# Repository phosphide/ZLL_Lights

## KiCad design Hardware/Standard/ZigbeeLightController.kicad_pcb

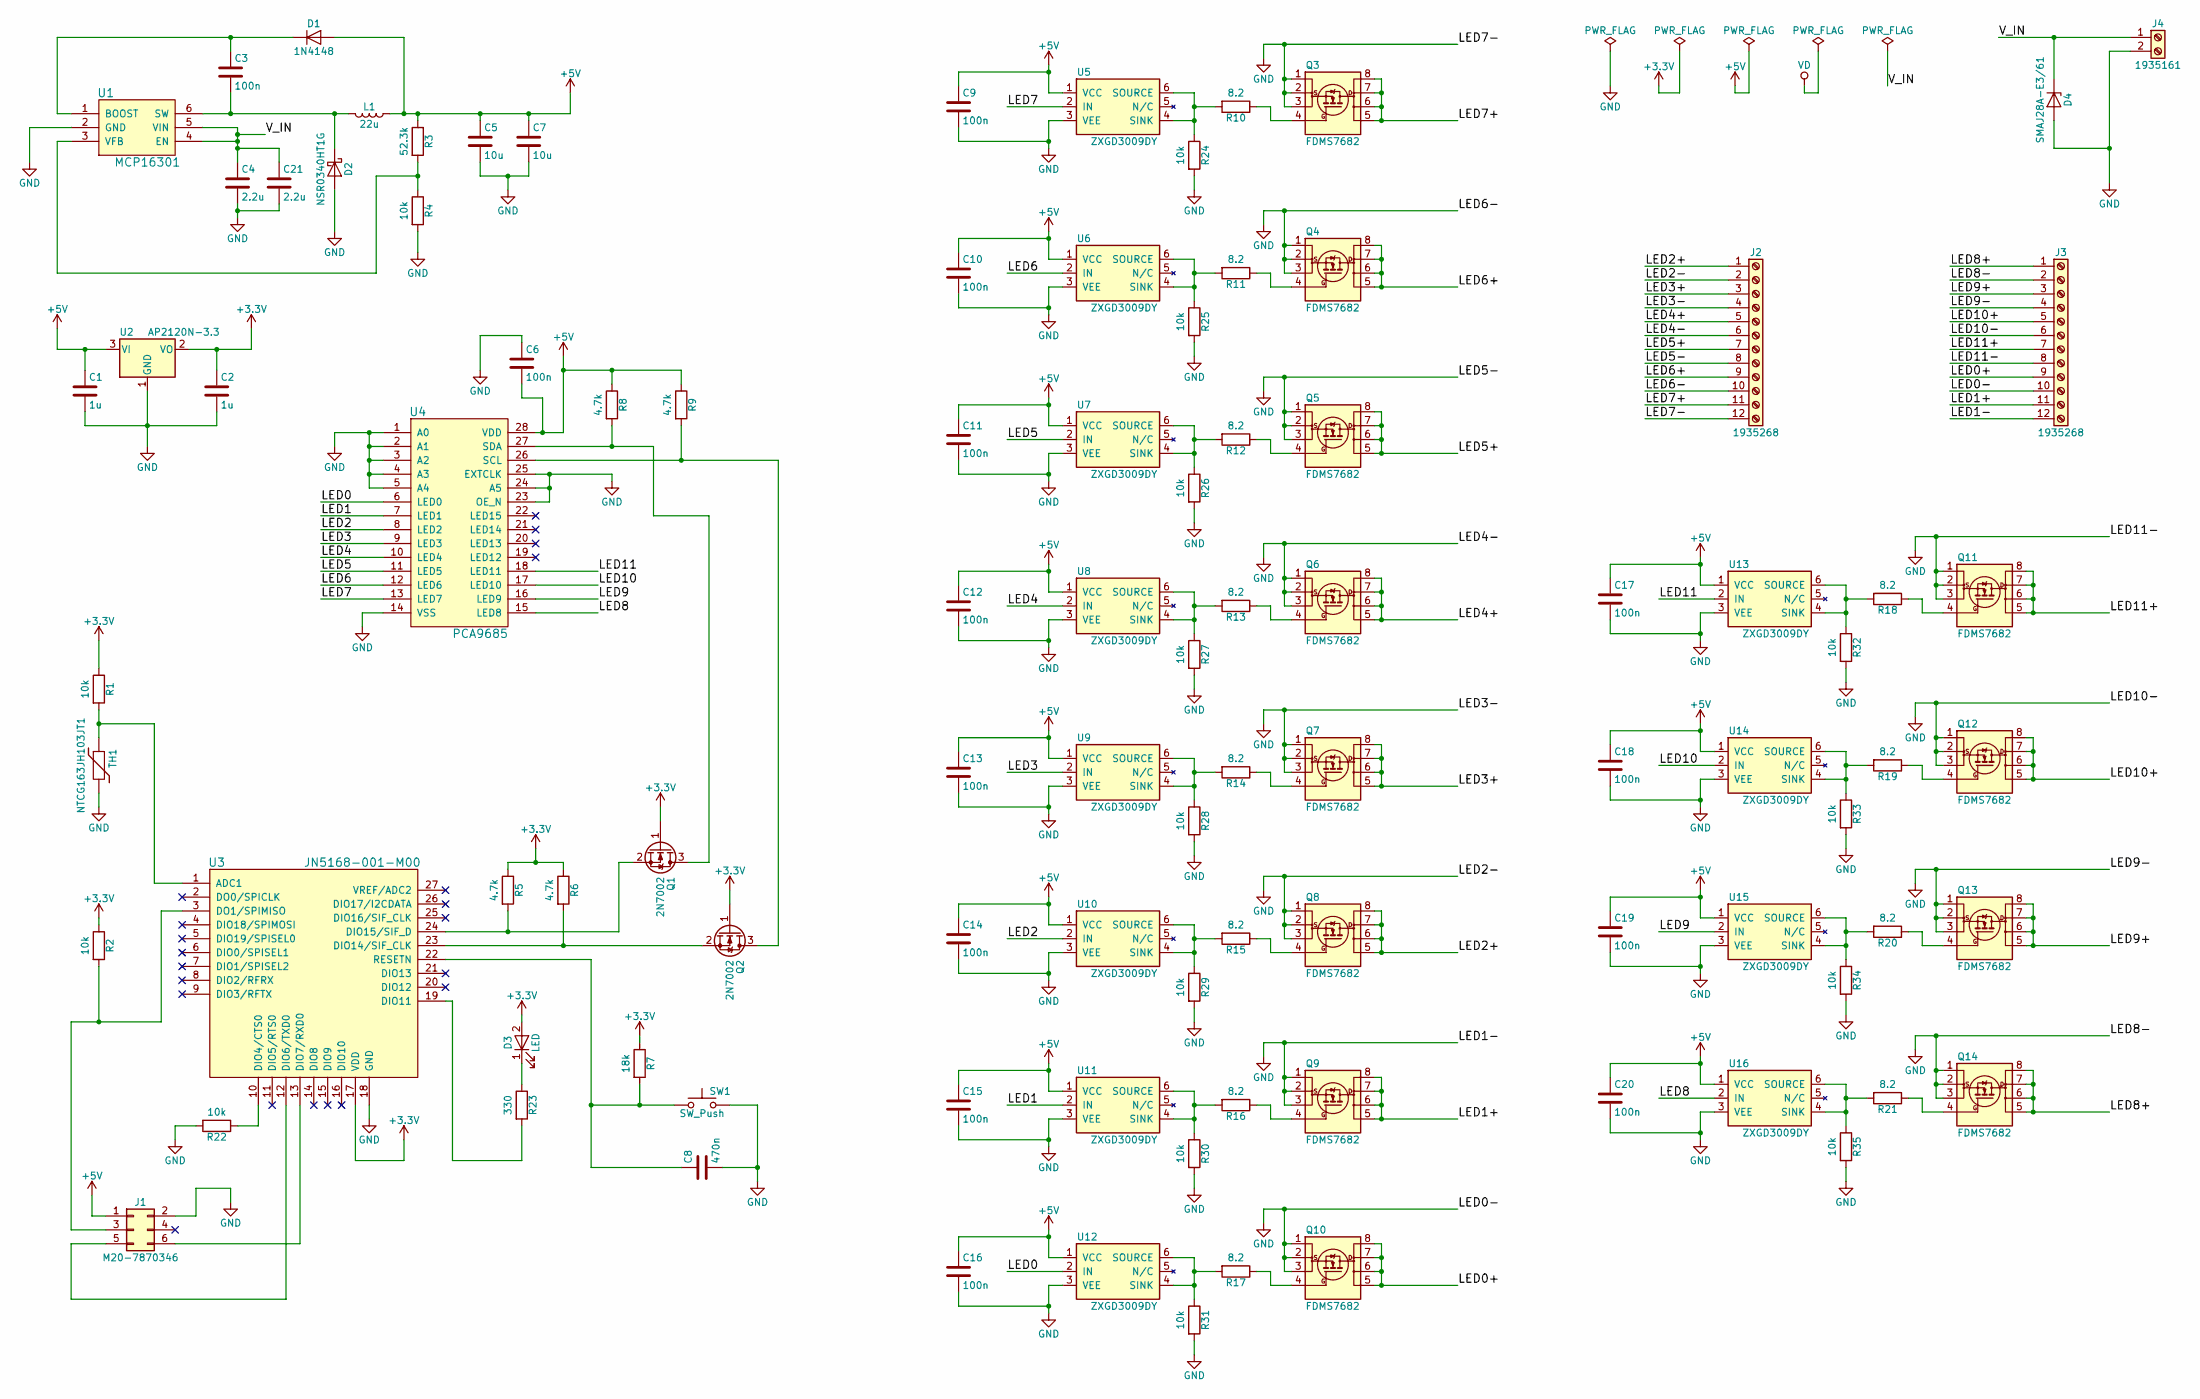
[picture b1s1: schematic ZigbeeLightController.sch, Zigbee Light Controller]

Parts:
C1, C2: 1u; C_0805
C3, C6, C9, C10, C11, C12, C13, C14, C15, C16, C17, C18, C19, C20: 100n; C_0603
C4, C21: 2.2u; C_1206
C5, C7: 10u; C_1206
C8: 470n; C_0603
D1: 1N4148; D_SOD-123
D2: NSR0340HT1G; D_SOD-323
D3: LED; D_0805_LED
D4: SMAJ28A-E3/61; D_SMA
J1: M20-7870346; Pin_Header_Straight_2x03_Pitch2.54mm_SMD
J2, J3: 1935268; TerminalBlock_Philmore_TB13x_12x5mm_Straight
J4: 1935161; TerminalBlock_Philmore_TB132_02x5mm_Straight
L1: 22u; L_Taiyo-Yuden_NR-50xx
Q1, Q2: 2N7002; SOT-23
Q3, Q4, Q5, Q6, Q7, Q8, Q9, Q10, Q11, Q12, Q13, Q14: FDMS7682; Power56_Vias
R1, R2, R4, R22, R24, R25, R26, R27, R28, R29, R30, R31, R32, R33, R34, R35: 10k; R_0603
R3: 52.3k; R_0603
R5, R6, R8, R9: 4.7k; R_0603
R7: 18k; R_0603
R10, R11, R12, R13, R14, R15, R16, R17, R18, R19, R20, R21: 8.2; R_0603
R23: 330; R_0603
SW1: SW_Push; PTS645SM43SMTR_92_LFS
TH1: NTCG163JH103JT1; R_0603
U1: MCP16301; SOT-23-6
U2: AP2120N-3.3; SOT-23
U3: JN5168-001-M00; JN5168-001
U4: PCA9685; TSSOP-28
U5, U6, U7, U8, U9, U10, U11, U12, U13, U14, U15, U16: ZXGD3009DY; SOT-363_SC-70-6

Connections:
+3V3: C2.1, D3.2 (A), Q1.1 (G), Q2.1 (G), R1.1, R2.1, R5.1, R6.1, R7.1, U2.2 (VO), U3.17 (VDD); also elsewhere on the board
+5V: C1.1, C5.1, C6.2, C7.1, C9.1, C10.1, C11.1, C12.1, C13.1, C14.1, C15.1, C16.1, C17.1, C18.1, C19.1, C20.1, D1.2 (A), J1.1, L1.1, R3.1, R8.1, R9.1, U2.3 (VI), U4.28 (VDD), U5.1 (VCC), U6.1 (VCC), U7.1 (VCC), U8.1 (VCC), U9.1 (VCC), U10.1 (VCC), U11.1 (VCC), U12.1 (VCC), U13.1 (VCC), U14.1 (VCC), U15.1 (VCC), U16.1 (VCC); also elsewhere on the board
/LED0: U4.6 (LED0), U12.2 (IN)
/LED0+: J3.9, Q10.5 (D), Q10.6 (D), Q10.7 (D), Q10.8 (D)
/LED1: U4.7 (LED1), U11.2 (IN)
/LED1+: J3.11, Q9.5 (D), Q9.6 (D), Q9.7 (D), Q9.8 (D)
/LED2: U4.8 (LED2), U10.2 (IN)
/LED2+: J2.1, Q8.5 (D), Q8.6 (D), Q8.7 (D), Q8.8 (D)
/LED3: U4.9 (LED3), U9.2 (IN)
/LED3+: J2.3, Q7.5 (D), Q7.6 (D), Q7.7 (D), Q7.8 (D)
/LED4: U4.10 (LED4), U8.2 (IN)
/LED4+: J2.5, Q6.5 (D), Q6.6 (D), Q6.7 (D), Q6.8 (D)
/LED5: U4.11 (LED5), U7.2 (IN)
/LED5+: J2.7, Q5.5 (D), Q5.6 (D), Q5.7 (D), Q5.8 (D)
/LED6: U4.12 (LED6), U6.2 (IN)
/LED6+: J2.9, Q4.5 (D), Q4.6 (D), Q4.7 (D), Q4.8 (D)
/LED7: U4.13 (LED7), U5.2 (IN); also elsewhere on the board
/LED7+: J2.11, Q3.5 (D), Q3.6 (D), Q3.7 (D), Q3.8 (D)
/LED8: U4.15 (LED8), U16.2 (IN)
/LED8+: J3.1, Q14.5 (D), Q14.6 (D), Q14.7 (D), Q14.8 (D)
/LED9: U4.16 (LED9), U15.2 (IN); also elsewhere on the board
/LED9+: J3.3, Q13.5 (D), Q13.6 (D), Q13.7 (D), Q13.8 (D)
/LED10: U4.17 (LED10), U14.2 (IN)
/LED10+: J3.5, Q12.5 (D), Q12.6 (D), Q12.7 (D), Q12.8 (D)
/LED11: U4.18 (LED11), U13.2 (IN)
/LED11+: J3.7, Q11.5 (D), Q11.6 (D), Q11.7 (D), Q11.8 (D)
/V_IN: C4.1, C21.1, D4.1 (K), J4.1, U1.4 (EN), U1.5 (VIN)
GND: C1.2, C2.2, C4.2, C5.2, C6.1, C7.2, C8.2, C9.2, C10.2, C11.2, C12.2, C13.2, C14.2, C15.2, C16.2, C17.2, C18.2, C19.2, C20.2, C21.2, D2.2 (A), D4.2 (A), J1.2, J2.2, J2.4, J2.6, J2.8, J2.10, J2.12, J3.2, J3.4, J3.6, J3.8, J3.10, J3.12, J4.2, Q3.1 (S), Q3.2 (S), Q3.3 (S), Q4.1 (S), Q4.2 (S), Q4.3 (S), Q5.1 (S), Q5.2 (S), Q5.3 (S), Q6.1 (S), Q6.2 (S), Q6.3 (S), Q7.1 (S), Q7.2 (S), Q7.3 (S), Q8.1 (S), Q8.2 (S), Q8.3 (S), Q9.1 (S), Q9.2 (S), Q9.3 (S), Q10.1 (S), Q10.2 (S), Q10.3 (S), Q11.1 (S), Q11.2 (S), Q11.3 (S), Q12.1 (S), Q12.2 (S), Q12.3 (S), Q13.1 (S), Q13.2 (S), Q13.3 (S), Q14.1 (S), Q14.2 (S), Q14.3 (S), R4.2, R22.2, R24.2, R25.2, R26.2, R27.2, R28.2, R29.2, R30.2, R31.2, R32.2, R33.2, R34.2, R35.2, SW1.2, TH1.2, U1.2 (GND), U2.1 (GND), U3.18 (GND), U4.1 (A0), U4.2 (A1), U4.3 (A2), U4.4 (A3), U4.5 (A4), U4.14 (VSS), U4.23 (OE_N), U4.24 (A5), U4.25 (EXTCLK), U5.3 (VEE), U6.3 (VEE), U7.3 (VEE), U8.3 (VEE), U9.3 (VEE), U10.3 (VEE), U11.3 (VEE), U12.3 (VEE), U13.3 (VEE), U14.3 (VEE), U15.3 (VEE), U16.3 (VEE); also elsewhere on the board
unnamed: C3.1, D1.1 (K), U1.1 (BOOST)
unnamed: C3.2, D2.1 (K), L1.2, U1.6 (SW)
unnamed: C8.1, R7.2, SW1.1, U3.22 (RESETN)
unnamed: D3.1 (K), R23.1
unnamed: J1.3, R2.2, U3.3 (DO1/SPIMISO)
unnamed: J1.5, U3.12 (DIO6/TXD0)
unnamed: J1.6, U3.13 (DIO7/RXD0)
unnamed: Q1.2 (S), R5.2, U3.24 (DIO15/SIF_D)
unnamed 37: Q1.3 (D), R8.2, U4.27 (SDA); also elsewhere on the board
unnamed: Q2.2 (S), R6.2, U3.23 (DIO14/SIF_CLK)
unnamed 39: Q2.3 (D), R9.2, U4.26 (SCL); also elsewhere on the board
unnamed: Q3.4 (G), R10.1
unnamed: Q4.4 (G), R11.1
unnamed: Q5.4 (G), R12.1
unnamed: Q6.4 (G), R13.1
unnamed: Q7.4 (G), R14.1
unnamed: Q8.4 (G), R15.1
unnamed: Q9.4 (G), R16.1
unnamed: Q10.4 (G), R17.1
unnamed: Q11.4 (G), R18.1
unnamed: Q12.4 (G), R19.1
unnamed: Q13.4 (G), R20.1
unnamed: Q14.4 (G), R21.1
unnamed: R1.2, TH1.1, U3.1 (ADC1)
unnamed: R3.2, R4.1, U1.3 (VFB)
unnamed: R10.2, R24.1, U5.4 (SINK), U5.6 (SOURCE)
unnamed: R11.2, R25.1, U6.4 (SINK), U6.6 (SOURCE)
unnamed: R12.2, R26.1, U7.4 (SINK), U7.6 (SOURCE)
unnamed: R13.2, R27.1, U8.4 (SINK), U8.6 (SOURCE)
unnamed: R14.2, R28.1, U9.4 (SINK), U9.6 (SOURCE)
unnamed: R15.2, R29.1, U10.4 (SINK), U10.6 (SOURCE)
unnamed: R16.2, R30.1, U11.4 (SINK), U11.6 (SOURCE)
unnamed: R17.2, R31.1, U12.4 (SINK), U12.6 (SOURCE)
unnamed: R18.2, R32.1, U13.4 (SINK), U13.6 (SOURCE)
unnamed: R19.2, R33.1, U14.4 (SINK), U14.6 (SOURCE)
unnamed: R20.2, R34.1, U15.4 (SINK), U15.6 (SOURCE)
unnamed: R21.2, R35.1, U16.4 (SINK), U16.6 (SOURCE)
unnamed: R22.1, U3.10 (DIO4/CTS0)
unnamed: R23.2, U3.19 (DIO11)

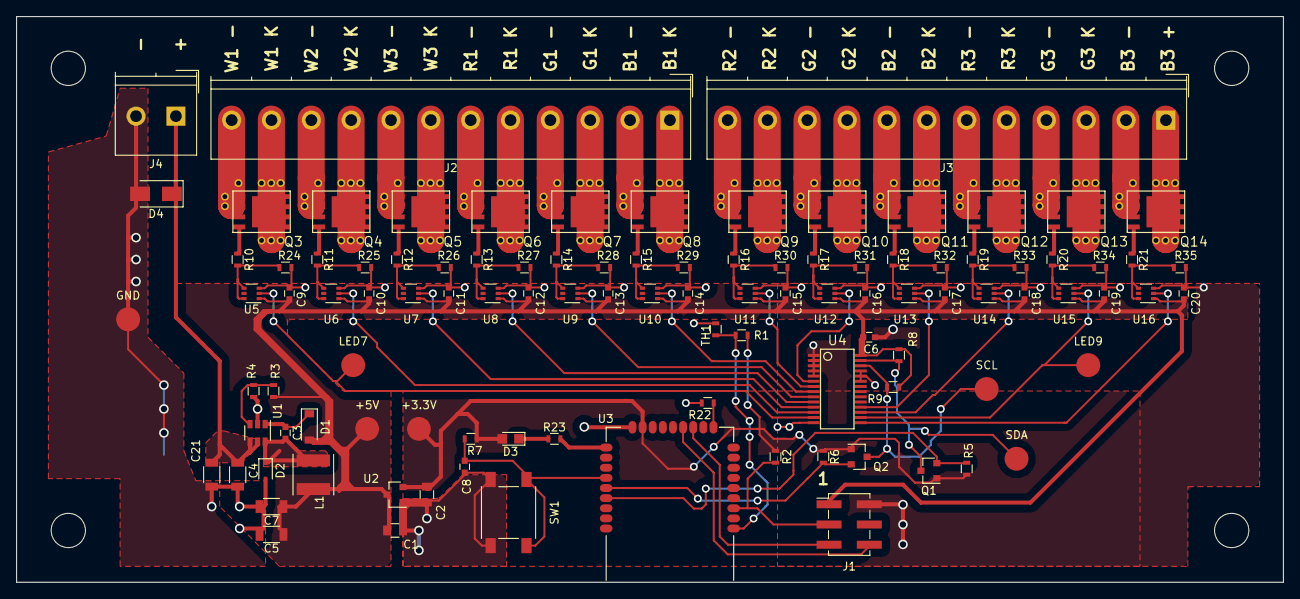
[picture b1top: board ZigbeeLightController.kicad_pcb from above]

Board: 2 copper layers, 159.0 x 71.0 mm, 104 parts (0 on the bottom side), 67 nets.

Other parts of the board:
+3.3V, +5V: Measurement_Point_Round-SMD-Pad_Big
GND: Measurement_Point_Round-SMD-Pad_Big
LED7, LED9: Measurement_Point_Round-SMD-Pad_Big
SCL: Measurement_Point_Round-SMD-Pad_Big
SDA: Measurement_Point_Round-SMD-Pad_Big

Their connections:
+3V3: +3.3V.1; also elsewhere on the board
+5V: +5V.1; also elsewhere on the board
/LED7: LED7.1; also elsewhere on the board
/LED9: LED9.1; also elsewhere on the board
GND: GND.1; also elsewhere on the board
unnamed 37: SDA.1; also elsewhere on the board
unnamed 39: SCL.1; also elsewhere on the board

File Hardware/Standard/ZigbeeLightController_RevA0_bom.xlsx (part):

Ref | Value | Footprint | Notes | Part number | Mouser reference
C1 | 1u | Capacitors_SMD:C_0805 | > 6V, X?R | GRM21BR71C105KA01L | 81-GRM40X105K16L
C2 | 1u | Capacitors_SMD:C_0805 | > 6V, X?R | GRM21BR71C105KA01L | 81-GRM40X105K16L
C3 | 100n | Capacitors_SMD:C_0603 | anything will do | 06033C104KAT2A | 581-06033C104KAT2A
C4 | 2.2u | Capacitors_SMD:C_1206 | > 40 V, X?R | UMK316B7225KL-T | 963-UMK316B7225KL-T
C5 | 10u | Capacitors_SMD:C_1206 | > 6V, X?R | GRM319R61E106KA12D | 81-GRM319R61E106KA2D
C6 | 100n | Capacitors_SMD:C_0603 | anything will do | 06033C104KAT2A | 581-06033C104KAT2A
C7 | 10u | Capacitors_SMD:C_1206 | > 6V, X?R | GRM319R61E106KA12D | 81-GRM319R61E106KA2D
C8 | 470n | Capacitors_SMD:C_0603 | anything will do | TMK107BJ474KA-T | 963-TMK107BJ474KA-T
C9 | 100n | Capacitors_SMD:C_0603 | anything will do | 06033C104KAT2A | 581-06033C104KAT2A
C10 | 100n | Capacitors_SMD:C_0603 | anything will do | 06033C104KAT2A | 581-06033C104KAT2A
C11 | 100n | Capacitors_SMD:C_0603 | anything will do | 06033C104KAT2A | 581-06033C104KAT2A
C12 | 100n | Capacitors_SMD:C_0603 | anything will do | 06033C104KAT2A | 581-06033C104KAT2A
C13 | 100n | Capacitors_SMD:C_0603 | anything will do | 06033C104KAT2A | 581-06033C104KAT2A
C14 | 100n | Capacitors_SMD:C_0603 | anything will do | 06033C104KAT2A | 581-06033C104KAT2A
C15 | 100n | Capacitors_SMD:C_0603 | anything will do | 06033C104KAT2A | 581-06033C104KAT2A
C16 | 100n | Capacitors_SMD:C_0603 | anything will do | 06033C104KAT2A | 581-06033C104KAT2A
C17 | 100n | Capacitors_SMD:C_0603 | anything will do | 06033C104KAT2A | 581-06033C104KAT2A
C18 | 100n | Capacitors_SMD:C_0603 | anything will do | 06033C104KAT2A | 581-06033C104KAT2A
C19 | 100n | Capacitors_SMD:C_0603 | anything will do | 06033C104KAT2A | 581-06033C104KAT2A
C20 | 100n | Capacitors_SMD:C_0603 | anything will do | 06033C104KAT2A | 581-06033C104KAT2A
C21 | 2.2u | Capacitors_SMD:C_1206 | > 40 V, X?R | UMK316B7225KL-T | 963-UMK316B7225KL-T
D1 | 1N4148 | Diodes_SMD:D_SOD-123 | any 1N4148 will do | 1N4148W-TP | 833-1N4148W-TP
D2 | NSR0340HT1G | Diodes_SMD:D_SOD-323 |  | NSR0340HT1G | 863-NSR0340HT1G
D3 | LED | Diodes_SMD:D_0805 | can substitute, but may need to update R23 and footprint | LG R971-KN-1 | 720-LGR971-KN-1
D4 | SMAJ28A-E3/61 | Diodes_SMD:D_SMA |  | SMAJ28A-E3/61 | 625-SMAJ28A-E3
J1 | M20-7870346 | see datasheet |  | M20-7870346 | 855-M20-7870346
J2 | 1935268 | see datasheet |  | 1935268 | 651-1935268
J3 | 1935268 | see datasheet |  | 1935268 | 651-1935268
J4 | 1935161 | see datasheet |  | 1935161 | 651-1935161
L1 | 22u | Inductors_SMD:L_Taiyo-Yuden_NR-50xx |  | NRS5020T220MMGJ | 963-NRS5020T220MMGJ
Q1 | 2N7002 | TO_SOT_Packages_SMD:SOT-23 | anything will do | 2N7002P,215 | 771-2N7002P-215
Q2 | 2N7002 | TO_SOT_Packages_SMD:SOT-23 | anything will do | 2N7002P,215 | 771-2N7002P-215
Q3 | FDMS7682 | zll_lib:Power56_Vias |  | FDMS7682 | 512-FDMS7682
Q4 | FDMS7682 | zll_lib:Power56_Vias |  | FDMS7682 | 512-FDMS7682
Q5 | FDMS7682 | zll_lib:Power56_Vias |  | FDMS7682 | 512-FDMS7682
Q6 | FDMS7682 | zll_lib:Power56_Vias |  | FDMS7682 | 512-FDMS7682
Q7 | FDMS7682 | zll_lib:Power56_Vias |  | FDMS7682 | 512-FDMS7682
Q8 | FDMS7682 | zll_lib:Power56_Vias |  | FDMS7682 | 512-FDMS7682
Q9 | FDMS7682 | zll_lib:Power56_Vias |  | FDMS7682 | 512-FDMS7682
Q10 | FDMS7682 | zll_lib:Power56_Vias |  | FDMS7682 | 512-FDMS7682
Q11 | FDMS7682 | zll_lib:Power56_Vias |  | FDMS7682 | 512-FDMS7682
Q12 | FDMS7682 | zll_lib:Power56_Vias |  | FDMS7682 | 512-FDMS7682
Q13 | FDMS7682 | zll_lib:Power56_Vias |  | FDMS7682 | 512-FDMS7682
Q14 | FDMS7682 | zll_lib:Power56_Vias |  | FDMS7682 | 512-FDMS7682
R1 | 10k | Resistors_SMD:R_0603 | anything will do | RC0603FR-0710KL | 603-RC0603FR-0710KL
R2 | 100k | Resistors_SMD:R_0603 | anything will do | RC0603JR-07100KL | 603-RC0603JR-07100KL
R3 | 52.3k | Resistors_SMD:R_0603 | must be < 1% | RC0402FR-0752K3L | 603-RC0402FR-0752K3L
R4 | 10k | Resistors_SMD:R_0603 | must be < 1% | RC0603FR-0710KL | 603-RC0603FR-0710KL
R5 | 4.7k | Resistors_SMD:R_0603 | anything will do | RC0603JR-074K7L | 603-RC0603JR-074K7L
R6 | 4.7k | Resistors_SMD:R_0603 | anything will do | RC0603JR-074K7L | 603-RC0603JR-074K7L
R7 | 18k | Resistors_SMD:R_0603 | anything will do | RC0603JR-0718KL | 603-RC0603JR-0718KL
R8 | 4.7k | Resistors_SMD:R_0603 | anything will do | RC0603JR-074K7L | 603-RC0603JR-074K7L
R9 | 4.7k | Resistors_SMD:R_0603 | anything will do | RC0603JR-074K7L | 603-RC0603JR-074K7L
R10 | 8.1999999999999993 | Resistors_SMD:R_0603 | anything will do | RC0603JR-078R2L | 603-RC0603JR-078R2L
R11 | 8.1999999999999993 | Resistors_SMD:R_0603 | anything will do | RC0603JR-078R2L | 603-RC0603JR-078R2L
R12 | 8.1999999999999993 | Resistors_SMD:R_0603 | anything will do | RC0603JR-078R2L | 603-RC0603JR-078R2L
R13 | 8.1999999999999993 | Resistors_SMD:R_0603 | anything will do | RC0603JR-078R2L | 603-RC0603JR-078R2L
R14 | 8.1999999999999993 | Resistors_SMD:R_0603 | anything will do | RC0603JR-078R2L | 603-RC0603JR-078R2L
R15 | 8.1999999999999993 | Resistors_SMD:R_0603 | anything will do | RC0603JR-078R2L | 603-RC0603JR-078R2L
R16 | 8.1999999999999993 | Resistors_SMD:R_0603 | anything will do | RC0603JR-078R2L | 603-RC0603JR-078R2L
R17 | 8.1999999999999993 | Resistors_SMD:R_0603 | anything will do | RC0603JR-078R2L | 603-RC0603JR-078R2L
R18 | 8.1999999999999993 | Resistors_SMD:R_0603 | anything will do | RC0603JR-078R2L | 603-RC0603JR-078R2L
R19 | 8.1999999999999993 | Resistors_SMD:R_0603 | anything will do | RC0603JR-078R2L | 603-RC0603JR-078R2L
R20 | 8.1999999999999993 | Resistors_SMD:R_0603 | anything will do | RC0603JR-078R2L | 603-RC0603JR-078R2L
R21 | 8.1999999999999993 | Resistors_SMD:R_0603 | anything will do | RC0603JR-078R2L | 603-RC0603JR-078R2L
R22 | 10k | Resistors_SMD:R_0603 | anything will do | RC0603FR-0710KL | 603-RC0603FR-0710KL
R23 | 330 | Resistors_SMD:R_0603 | anything will do | RC0603JR-07330RL | 603-RC0603JR-07330RL
R24 | 10k | Resistors_SMD:R_0603 | anything will do | RC0603FR-0710KL | 603-RC0603FR-0710KL
R25 | 10k | Resistors_SMD:R_0603 | anything will do | RC0603FR-0710KL | 603-RC0603FR-0710KL
R26 | 10k | Resistors_SMD:R_0603 | anything will do | RC0603FR-0710KL | 603-RC0603FR-0710KL
R27 | 10k | Resistors_SMD:R_0603 | anything will do | RC0603FR-0710KL | 603-RC0603FR-0710KL
R28 | 10k | Resistors_SMD:R_0603 | anything will do | RC0603FR-0710KL | 603-RC0603FR-0710KL
R29 | 10k | Resistors_SMD:R_0603 | anything will do | RC0603FR-0710KL | 603-RC0603FR-0710KL
R30 | 10k | Resistors_SMD:R_0603 | anything will do | RC0603FR-0710KL | 603-RC0603FR-0710KL
R31 | 10k | Resistors_SMD:R_0603 | anything will do | RC0603FR-0710KL | 603-RC0603FR-0710KL
R32 | 10k | Resistors_SMD:R_0603 | anything will do | RC0603FR-0710KL | 603-RC0603FR-0710KL
R33 | 10k | Resistors_SMD:R_0603 | anything will do | RC0603FR-0710KL | 603-RC0603FR-0710KL
R34 | 10k | Resistors_SMD:R_0603 | anything will do | RC0603FR-0710KL | 603-RC0603FR-0710KL
R35 | 10k | Resistors_SMD:R_0603 | anything will do | RC0603FR-0710KL | 603-RC0603FR-0710KL
SW1 | SW_Push | zll_lib:PTS645SM43SMTR_92_LFS | can substitute, but may need to update footprint | PTS645SM43SMTR 92 LFS | 611-PTS645SM43SMTR92
TH1 | NTCG163JH103JT1 | Resistors_SMD:R_0603 | can substitute, but may need to update calibration in firmware | NTCG163JH103JT1 | 810-NTCG163JH103JT1
U1 | MCP16301 | TO_SOT_Packages_SMD:SOT-23-6 |  | MCP16301 | 579-MCP16301HT-E/CH
U2 | AP2120N-3.3 | TO_SOT_Packages_SMD:SOT-23 |  | AP2120N-3.3TRG1 | 621-AP2120N-3.3TRG1
U3 | JN5168-001-M00 | zll_lib:JN5168-001 |  | JN5168-001-M00Z | 771-JN5168-001-M00Z
U4 | PCA9685 | zll_lib:TSSOP-28 |  | PCA9685PW,118 | 771-PCA9685PW,118
U5 | ZXGD3009DY | TO_SOT_Packages_SMD:SOT-363_SC-70-6 |  | ZXGD3009DYTA | 621-ZXGD3009DYTA
U6 | ZXGD3009DY | TO_SOT_Packages_SMD:SOT-363_SC-70-6 |  | ZXGD3009DYTA | 621-ZXGD3009DYTA
U7 | ZXGD3009DY | TO_SOT_Packages_SMD:SOT-363_SC-70-6 |  | ZXGD3009DYTA | 621-ZXGD3009DYTA
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
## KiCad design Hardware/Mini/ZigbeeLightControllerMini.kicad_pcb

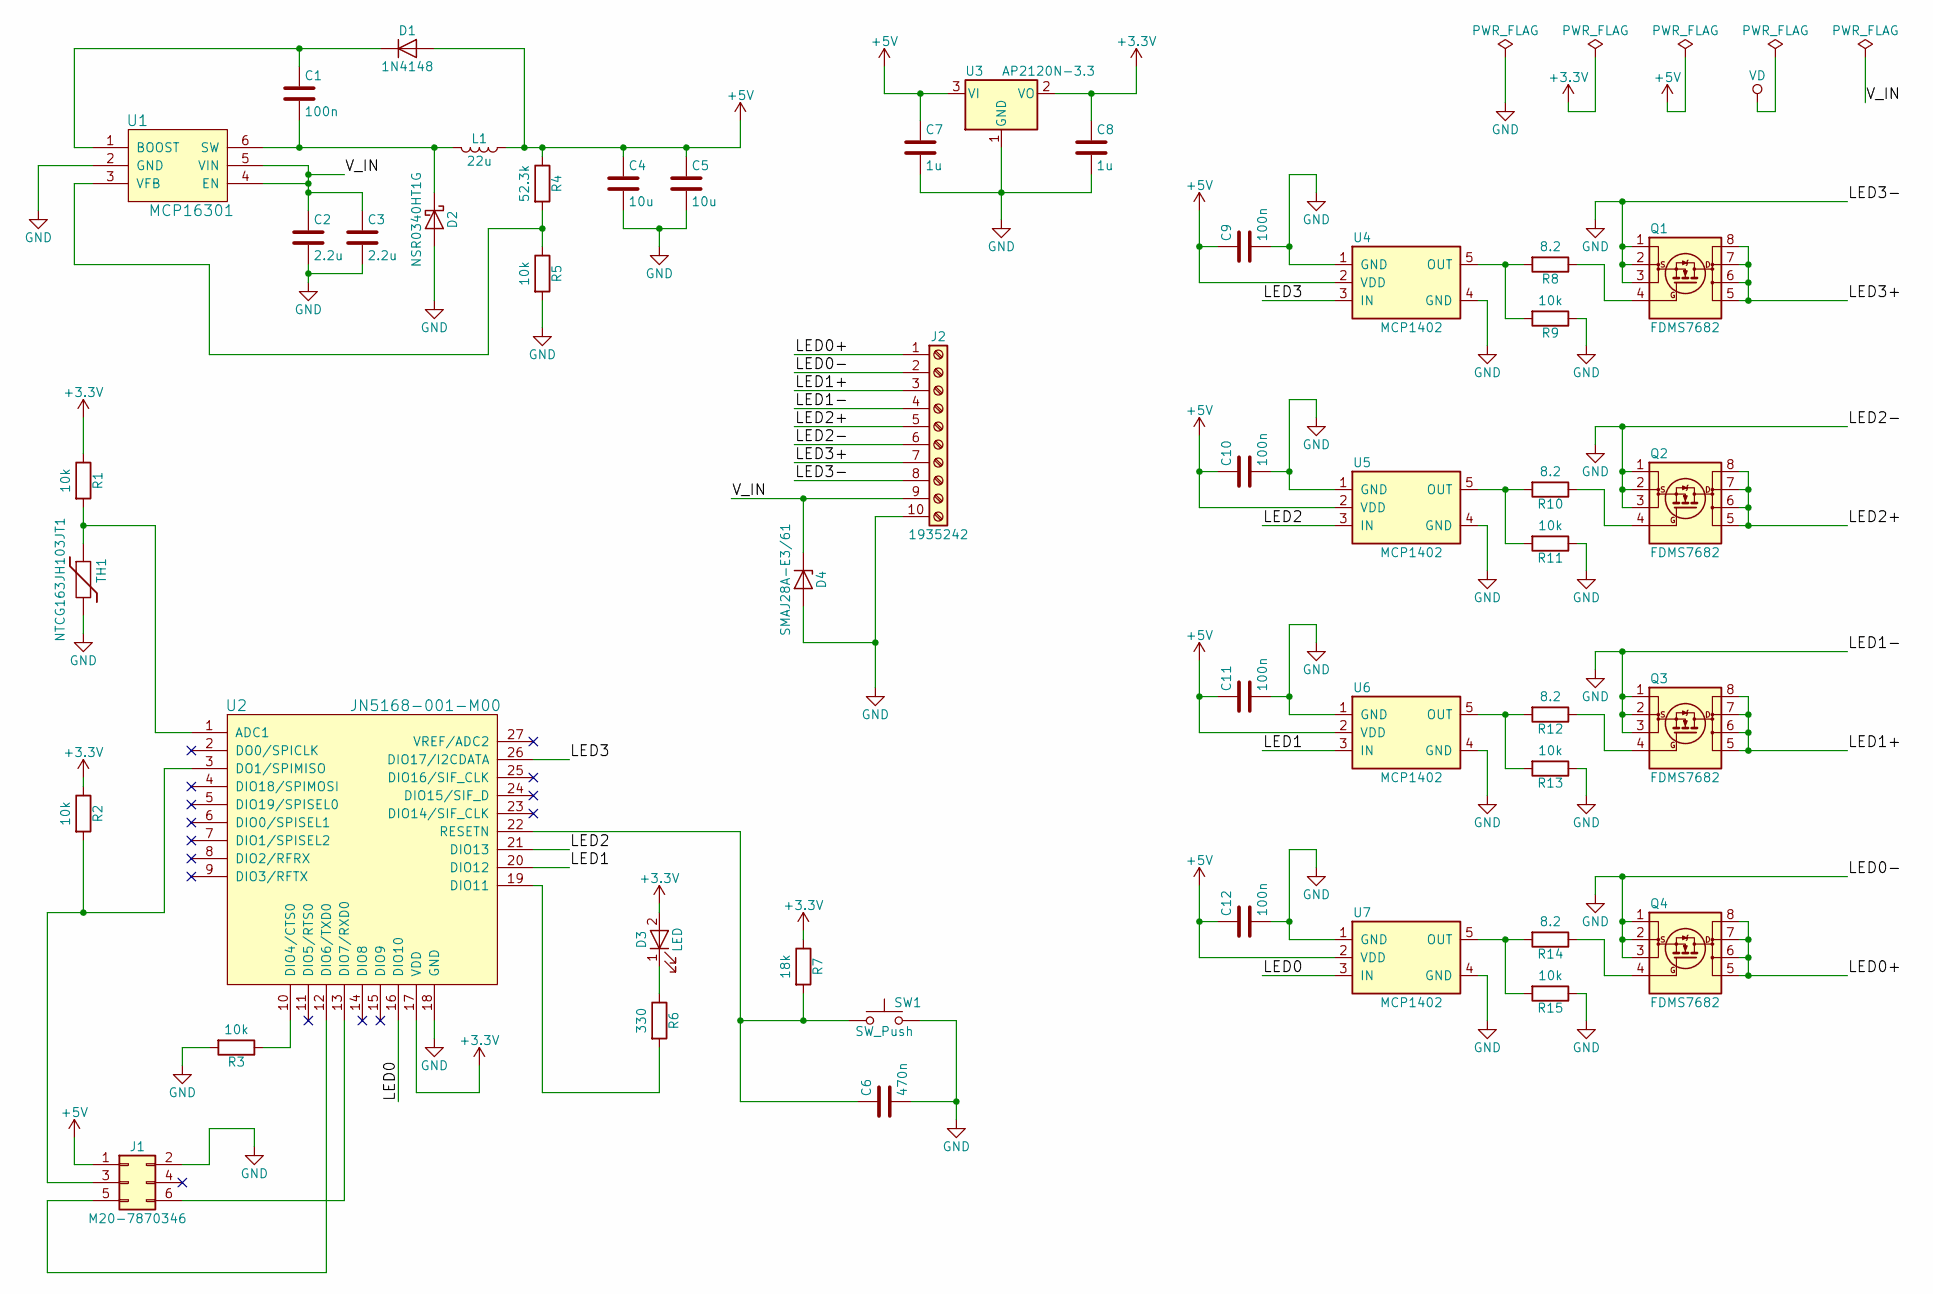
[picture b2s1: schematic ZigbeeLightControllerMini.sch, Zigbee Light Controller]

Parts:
C1, C9, C10, C11, C12: 100n; C_0603
C2, C3: 2.2u; C_1206
C4, C5: 10u; C_1206
C6: 470n; C_0603
C7, C8: 1u; C_0805
D1: 1N4148; D_SOD-123
D2: NSR0340HT1G; D_SOD-323
D3: LED; D_0805_LED
D4: SMAJ28A-E3/61; D_SMA
J1: M20-7870346; Pin_Header_Straight_2x03_Pitch2.54mm_SMD
J2: 1935242; TerminalBlock_Phoenix_MKDS1.5-10pol
L1: 22u; L_Taiyo-Yuden_NR-50xx
Q1, Q2, Q3, Q4: FDMS7682; Power56_Vias
R1, R2, R3, R5, R9, R11, R13, R15: 10k; R_0603
R4: 52.3k; R_0603
R6: 330; R_0603
R7: 18k; R_0603
R8, R10, R12, R14: 8.2; R_0603
SW1: SW_Push; PTS645SM43SMTR_92_LFS
TH1: NTCG163JH103JT1; R_0603
U1: MCP16301; SOT-23-6
U2: JN5168-001-M00; JN5168-001
U3: AP2120N-3.3; SOT-23
U4, U5, U6, U7: MCP1402; SOT-23-5

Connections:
+3V3: C8.1, D3.2 (A), R1.1, R2.1, R7.1, U2.17 (VDD), U3.2 (VO); also elsewhere on the board
+5V: C4.1, C5.1, C7.1, C9.1, C10.1, C11.1, C12.1, D1.2 (A), J1.1, L1.1, R4.1, U3.3 (VI), U4.2 (VDD), U5.2 (VDD), U6.2 (VDD), U7.2 (VDD); also elsewhere on the board
/LED0: U2.16 (DIO10), U7.3 (IN)
/LED0+: J2.1, Q4.5 (D), Q4.6 (D), Q4.7 (D), Q4.8 (D)
/LED1: U2.20 (DIO12), U6.3 (IN)
/LED1+: J2.3, Q3.5 (D), Q3.6 (D), Q3.7 (D), Q3.8 (D)
/LED2: U2.21 (DIO13), U5.3 (IN)
/LED2+: J2.5, Q2.5 (D), Q2.6 (D), Q2.7 (D), Q2.8 (D)
/LED3: U2.26 (DIO17/I2CDATA), U4.3 (IN)
/LED3+: J2.7, Q1.5 (D), Q1.6 (D), Q1.7 (D), Q1.8 (D)
/V_IN: C2.1, C3.1, D4.1 (K), J2.9, U1.4 (EN), U1.5 (VIN)
GND: C2.2, C3.2, C4.2, C5.2, C6.2, C7.2, C8.2, C9.2, C10.2, C11.2, C12.2, D2.2 (A), D4.2 (A), J1.2, J2.2, J2.4, J2.6, J2.8, J2.10, Q1.1 (S), Q1.2 (S), Q1.3 (S), Q2.1 (S), Q2.2 (S), Q2.3 (S), Q3.1 (S), Q3.2 (S), Q3.3 (S), Q4.1 (S), Q4.2 (S), Q4.3 (S), R3.2, R5.2, R9.1, R11.1, R13.1, R15.1, SW1.2, TH1.2, U1.2 (GND), U2.18 (GND), U3.1 (GND), U4.1 (GND), U4.4 (GND), U5.1 (GND), U5.4 (GND), U6.1 (GND), U6.4 (GND), U7.1 (GND), U7.4 (GND)
unnamed: C1.1, D1.1 (K), U1.1 (BOOST)
unnamed: C1.2, D2.1 (K), L1.2, U1.6 (SW)
unnamed: C6.1, R7.2, SW1.1, U2.22 (RESETN)
unnamed: D3.1 (K), R6.1
unnamed: J1.3, R2.2, U2.3 (DO1/SPIMISO)
unnamed: J1.5, U2.12 (DIO6/TXD0)
unnamed: J1.6, U2.13 (DIO7/RXD0)
unnamed: Q1.4 (G), R8.1
unnamed: Q2.4 (G), R10.1
unnamed: Q3.4 (G), R12.1
unnamed: Q4.4 (G), R14.1
unnamed: R1.2, TH1.1, U2.1 (ADC1)
unnamed: R3.1, U2.10 (DIO4/CTS0)
unnamed: R4.2, R5.1, U1.3 (VFB)
unnamed: R6.2, U2.19 (DIO11)
unnamed: R8.2, R9.2, U4.5 (OUT)
unnamed: R10.2, R11.2, U5.5 (OUT)
unnamed: R12.2, R13.2, U6.5 (OUT)
unnamed: R14.2, R15.2, U7.5 (OUT)

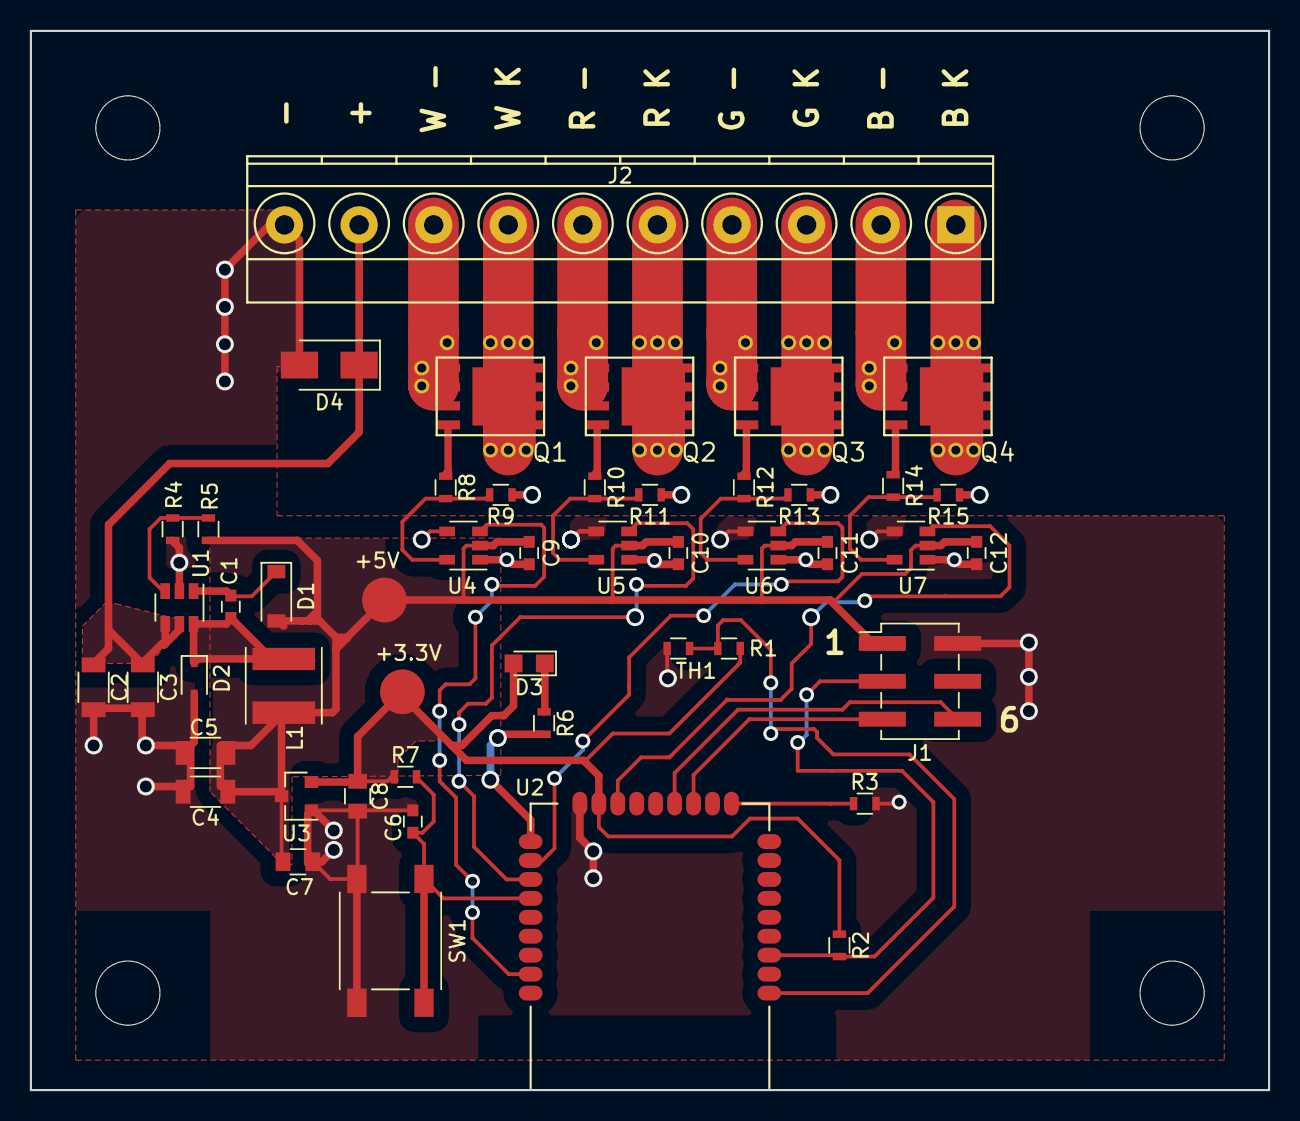
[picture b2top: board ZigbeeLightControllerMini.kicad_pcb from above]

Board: 2 copper layers, 83.0 x 71.0 mm, 49 parts (0 on the bottom side), 31 nets.

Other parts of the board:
+3.3V, +5V: Measurement_Point_Round-SMD-Pad_Big

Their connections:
+3V3: +3.3V.1; also elsewhere on the board
+5V: +5V.1; also elsewhere on the board

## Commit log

2017-11-24 Update to OS config for newer SDK
2017-11-25 Trimming down to one configuration and renaming it to MultiLight
2017-11-25 .project and .cproject were missed in the last commit
2017-12-04 Adding and registering endpoints for multiple dimmable/colour lights
2017-12-24 Adding PCA9685 driver
2017-12-25 Using makefile variables to set stack/heap size, since the .ld files don't seem to be doing anything
2017-12-25 Different endpoint controls now get routed to different bulb channels
2017-12-25 Scaling PWM values correctly for PCA9685
2017-12-28 Saving scene data for all endpoints, making sure vIdEffectTick has the correct prototype as required by API
2017-12-28 Fixing issue where group commands were not going to all endpoints
2017-12-28 Removing unneeded files
2017-12-28 Making APP_ZCL_vSetIdentifyTime (mostly) per-endpoint so that identify effects go to the correct endpoint
2017-12-29 Improvements to PCA9685 driver
2017-12-29 Fixing bug where switching from full-off to full-on would not work
2018-04-22 Adjusting PWM value based on gamma/intensity
2018-04-23 Adding ability to configure using serial port
2018-05-01 Adding hardware definition files
2018-05-06 Using simpler command format
2018-05-06 Measuring temperature using on-board NTC thermistor
2018-05-25 Disabling mono lights if computed white mode is active
2018-05-26 Adding computed white mode
2018-05-26 Maximum level is 254, not 255
2018-05-26 Using COMPUTED_WHITE_NONE instead of literal 0
2018-05-26 Bugfix: call to APP_vHandleIdentify was using wrong parameters
2018-05-26 Shutting off lights if board reaches a temperature limit
2018-05-27 Adding hardware definition files for mini version
2018-05-27 Standard hardware bugfixes: changed BOM to use correct 0603 part instead of 0402 part, widened pad for D3, changed R2 to 10k to reduce line item count, filling top layer
2018-05-27 Removing unnecessary kicad files
2018-05-28 Firmware updates for Mini version
2018-05-28 Adding .cproject that was missed in last commit, providing dummy ISR for Timer1 to appease linker
2018-05-30 Bugfix: variant wasn't being set correctly
2018-05-30 Fixing PCB fill issue, using - and K for LED terminals
2018-05-30 Adding serial config guide
2018-05-30 markdown formatting for serial config guide
2020-05-03 Started transition to UART-based control of slave driver MCU (via UART1)
